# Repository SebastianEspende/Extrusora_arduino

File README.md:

Firmware 1 es el codigo que ha sido probado y esta funcionando pero es bastante redundante
Firmware 2 es el codigo que esta sin probar, aunque deberia funcionar, es mas sencillo añadir nuevos items en el menu.

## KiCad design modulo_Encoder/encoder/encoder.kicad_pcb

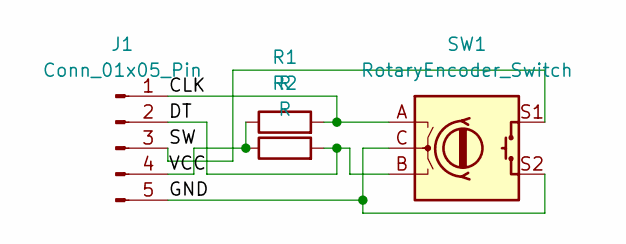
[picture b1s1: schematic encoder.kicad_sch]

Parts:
J1: Conn_01x05_Pin; PinHeader_1x05_P2.54mm_Vertical
R1, R2: R; R_Axial_DIN0411_L9.9mm_D3.6mm_P12.70mm_Horizontal
SW1: RotaryEncoder_Switch; RotaryEncoder_Alps_EC11E-Switch_Vertical_H20mm

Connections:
/CLK: J1.1, R1.2, SW1.A
/DT: J1.2, R2.2, SW1.B
/GND: J1.5, SW1.C, SW1.S2
/SW: J1.3, SW1.S1
/VCC: J1.4, R1.1, R2.1

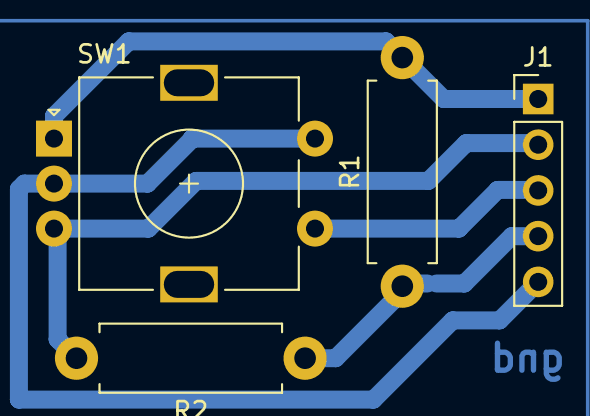
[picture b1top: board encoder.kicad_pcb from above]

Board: 2 copper layers, 4 parts (0 on the bottom side), 5 nets.

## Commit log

2023-12-15 Firmware2 y librerias
2023-12-15 Diseño de placas
